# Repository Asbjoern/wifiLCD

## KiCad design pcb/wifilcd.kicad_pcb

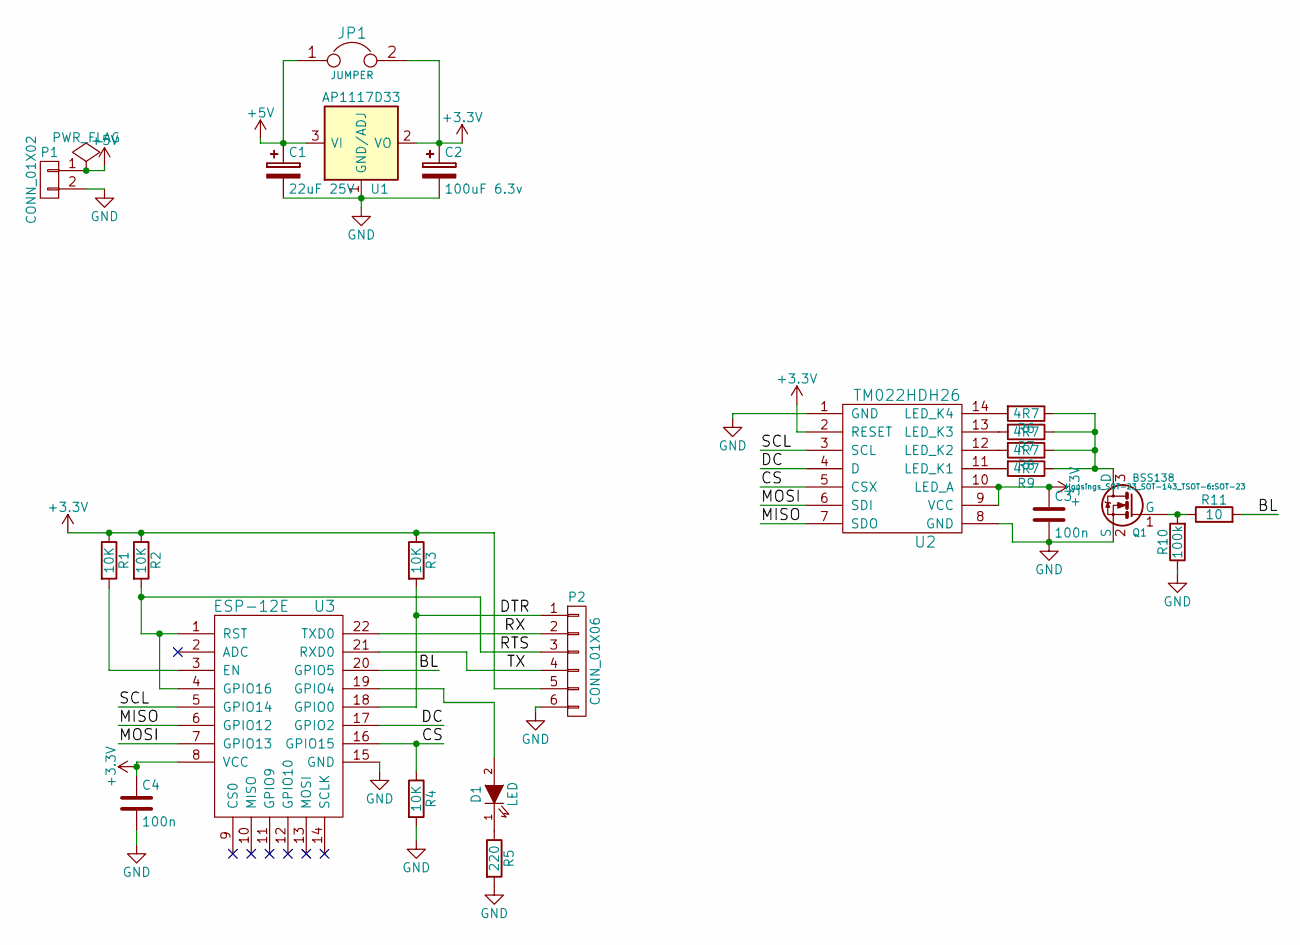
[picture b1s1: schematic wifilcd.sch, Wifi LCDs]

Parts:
C1: 22uF 25V; TantalC_SizeT_EIA-3528
C2: 100uF 6.3v; TantalC_SizeT_EIA-3528
C3, C4: 100n; C_0603
D1: LED; LED-0603
JP1: JUMPER; R_0603_HandSoldering
P1: CONN_01X02; Pin_Header_Angled_1x02
P2: CONN_01X06; Pin_Header_Angled_2x03
Q1: BSS138; SOT-23
R1, R2, R3, R4: 10K; R_0603
R5: 220; R_0603
R6, R7, R8, R9: 4R7; R_0603
R10: 100k; R_0603
R11: 10; R_0603
U1: AP1117D33; SOT-223
U2: TM022HDH26
U3: ESP-12E

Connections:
+3V3: C2.1, C3.1, C4.1, JP1.2, P2.5, R1.1, R2.1, R3.1, U1.2 (VO), U2.2 (RESET), U2.9 (VCC), U2.10 (LED_A), U3.8 (VCC)
+5V: C1.1, JP1.1, P1.1, U1.3 (VI)
/BL: R11.2, U3.20 (GPIO5)
/CS: R4.1, U2.5 (CSX), U3.16 (GPIO15)
/DC: U2.4 (D), U3.17 (GPIO2)
/DTR: P2.1, R3.2, U3.18 (GPIO0)
/MISO: U2.7 (SDO), U3.6 (GPIO12)
/MOSI: U2.6 (SDI), U3.7 (GPIO13)
/RTS: P2.3, R2.2, U3.1 (RST), U3.4 (GPIO16)
/RX: P2.2, U3.22 (TXD0)
/SCL: U2.3 (SCL), U3.5 (GPIO14)
/TX: P2.4, U3.21 (RXD0)
GND: C1.2, C2.2, C3.2, C4.2, P1.2, P2.6, Q1.2 (S), R4.2, R5.2, R10.1, U1.1 (GND/ADJ), U2.1 (GND), U2.8 (GND), U3.15 (GND)
unnamed: D1.1 (K), R5.1
unnamed: D1.2 (A), U3.19 (GPIO4)
unnamed: Q1.1 (G), R10.2, R11.1
unnamed: Q1.3 (D), R6.1, R7.1, R8.1, R9.1
unnamed: R1.2, U3.3 (EN)
unnamed: R6.2, U2.14 (LED_K4)
unnamed: R7.2, U2.13 (LED_K3)
unnamed: R8.2, U2.12 (LED_K2)
unnamed: R9.2, U2.11 (LED_K1)

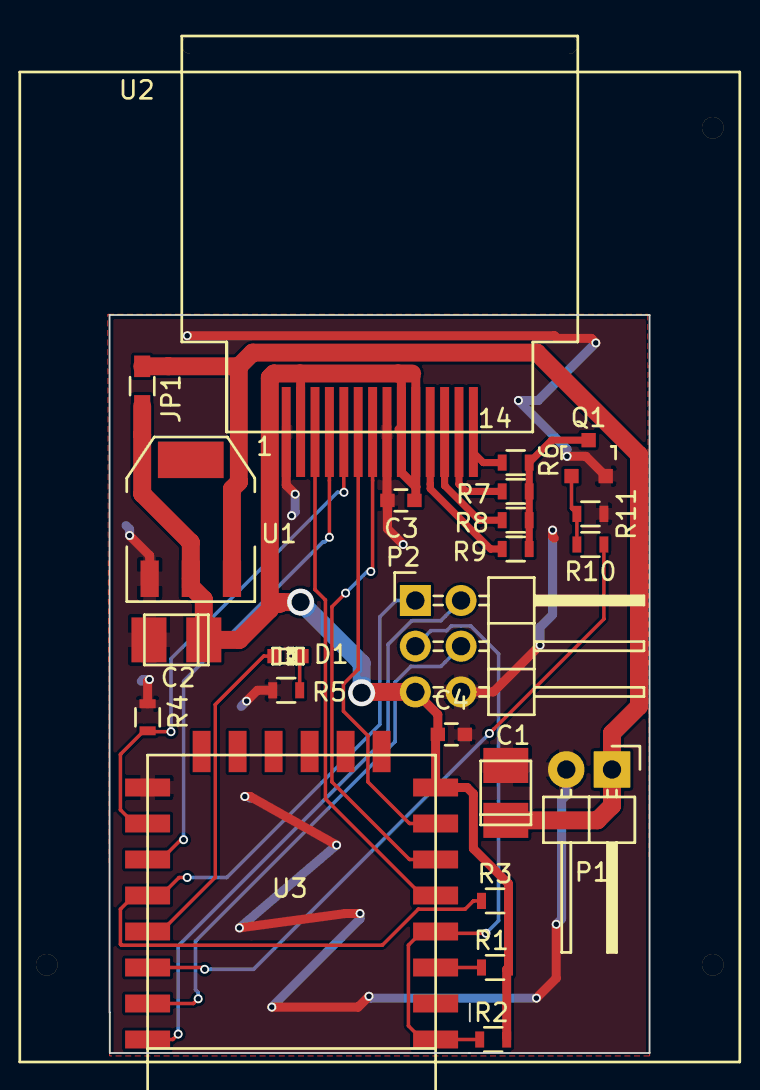
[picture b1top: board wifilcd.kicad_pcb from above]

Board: 2 copper layers, 30.0 x 41.0 mm, 23 parts (0 on the bottom side), 22 nets.

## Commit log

2015-06-20 Initial. Not properbly teste. PUT does not yet work with BMP files
2015-06-22 Added KiCad files for PCB
2015-06-22 PCB: Fixed library path
2015-06-22 Added support for backlight control
2015-06-22 POST argument for backlight is now parsed
2015-06-23 Backlight crashed if set in Setup(). Moved to LOOP Recovery AP now named WiFiLCD Recovery instead of name in settings.
2015-06-23 Fixed allowPUT switch + cleanup
2015-06-23 Added HTTP PUT of BMP files feature
2015-07-08 Switched to Adafruits LCD library
2015-07-08 Minor PCB changes
2015-07-08 Added OTA support. Second part accedently committed with Adafruit LCD commit
2015-07-08 Added Telnet Debug output
2015-07-23 Added progress update to OTA client
2015-07-23 Added OTA switch to webconfig
2016-02-23 Updated pcb to new KiCad
2016-02-23 Updated to SDK v.2.1.0-rc2
    Removed telnet debug server
    Optimized lcd
    Newest http library
    Check for firmware updates on boot.
